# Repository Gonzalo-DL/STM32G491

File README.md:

# STM32G491
Diseño STM32G491 con USB y con header para los pines.

Además Flash de 64MB (W25Q64JWZPIM) externa con QuadSPI y dos leds en PA0 y PA1.

Conexión por USB female micro b con Buck para 3.3v.

Vin hasta 5.5v con absolute max = 6.5v.

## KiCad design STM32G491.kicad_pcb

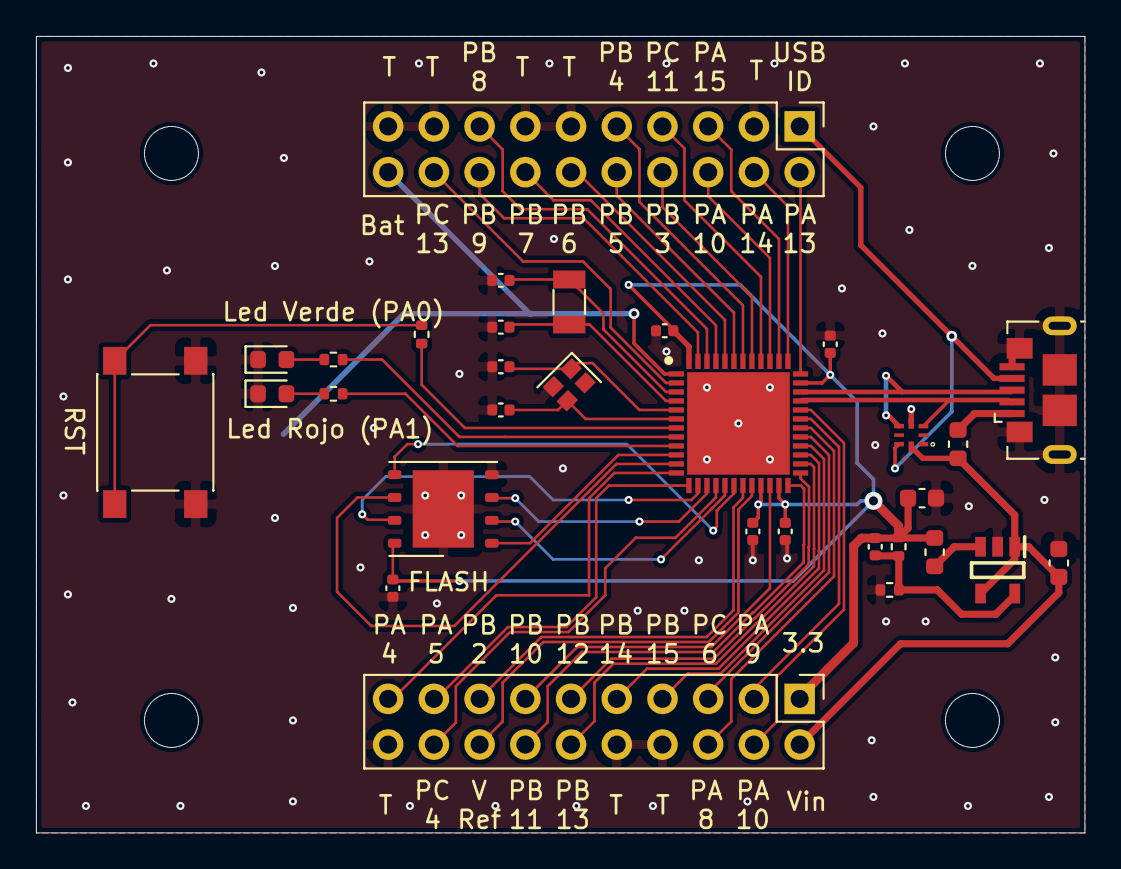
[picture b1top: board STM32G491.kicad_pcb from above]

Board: 2 copper layers, 58.2 x 44.2 mm, 32 parts (1 on the bottom side), 54 nets.

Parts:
32KHz_Crystal1: 32KHz crystal; Crystal_SMD_3215-2Pin_3.2x1.5mm
BUCK3.3: AUR9713AGH; SOT95P280X100-5N
Battery1: LIR2032; BatteryHolder_Keystone_1058_1x2032
C1(opt)1, C2(opt)1: 4p; C_0402_1005Metric
C3, C4: 12p; C_0402_1005Metric
C101, C102, C103, C104, C105: 100n; C_0402_1005Metric
C201: 4.7u; C_0603_1608Metric
C202: 10u; C_0603_1608Metric
C203: 13p; C_0402_1005Metric
Crystal_48MHz1: CX2016DB48000C0FPLC1; Crystal_SMD_2016-4Pin_2.0x1.6mm
EMI_VDDS_FILTER_USB1: BLM18HE152SN1D; L_0603_1608Metric
FLASH: W25Q64JWZPIM; WSON-8-1EP_6x5mm_P1.27mm_EP3.4x4.3mm
IC1: TPD6E004RSER; RSE0008A
J1, J2: Conn_02x10_Odd_Even; PinHeader_2x10_P2.54mm_Vertical
L101: 2.2u; L_0603_1608Metric
Led Rojo (PA1): LED; LED_0603_1608Metric
Led Verde (PA0): LED; LED_0603_1608Metric
R101: 450k; R_0402_1005Metric
R102: 100k; R_0402_1005Metric
RST: SW_DIP_x01; SW_SPST_PTS645
R_LED_ROJO1: 180; R_0402_1005Metric
R_LED_VERDE1: 220; R_0402_1005Metric
R_RST1: 100; R_0402_1005Metric
STM32: STM32G491CCU6; QFN50P700X700X60-49N-D
USB_IN1: USB_B_Micro; USB_Micro-B_GCT_USB3076-30-A

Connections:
/OSC32_IN: 32KHz_Crystal1.1, C3.1, STM32.3
/OSC32_OUT: 32KHz_Crystal1.2, C4.1, STM32.4
/OSC_IN: C1(opt)1.1, Crystal_48MHz1.1, STM32.5
/OSC_OUT: C2(opt)1.1, Crystal_48MHz1.3, STM32.6
/PA0: R_LED_VERDE1.1, STM32.8
/PA1: R_LED_ROJO1.1, STM32.9
/PA4: J2.19, STM32.12
/PA5: J2.17, STM32.13
/PA8: J2.6, STM32.30
/PA9: J2.3, STM32.31
/PA10: J2.4, STM32.32
/PA13: J1.2, STM32.36
/PA14: J1.4, STM32.37
/PA15: J1.5, STM32.38
/PB2: J2.15, STM32.19
/PB3: J1.8, STM32.41
/PB4: J1.9, STM32.42
/PB5: J1.10, STM32.43
/PB6: J1.12, STM32.44
/PB7: J1.14, STM32.45
/PB8-BOOT0: J1.15, STM32.46
/PB9: J1.16, STM32.47
/PB10: J2.13, STM32.22
/PB11: J2.14, STM32.24
/PB12: J2.11, STM32.25
/PB13: J2.12, STM32.26
/PB14: J2.9, STM32.27
/PB15: J2.7, STM32.28
/PC4: J2.18, STM32.16
/PC6: J2.5, STM32.29
/PC10: J1.6, STM32.39
/PC11: J1.7, STM32.40
/PC13: J1.18, STM32.2
/SCLK: FLASH.6, STM32.11
/SDIO0: FLASH.5, STM32.18
/SDIO1: FLASH.2, STM32.17
/SDIO2: FLASH.3, STM32.15
/SDIO3: FLASH.7, STM32.14
/USB_D+: IC1.5, STM32.34, USB_IN1.3
/USB_D-: IC1.3, STM32.33, USB_IN1.2
/USB_ID: IC1.7, J1.1, USB_IN1.4
/VBat: Battery1.1, J1.20, STM32.1
/VDD: C101.2, C102.2, C103.2, C104.2, C105.1, C202.1, C203.2, FLASH.8, J2.1, L101.2, R101.2, STM32.21, STM32.23, STM32.35, STM32.48
/VREF: J2.16, STM32.20
/Vin: BUCK3.3.1, BUCK3.3.4, C201.1, EMI_VDDS_FILTER_USB1.1, IC1.8, J2.2
/nCS: FLASH.1, STM32.10
/nRST: R_RST1.1, STM32.7
GND: BUCK3.3.2, Battery1.2, C1(opt)1.2, C2(opt)1.2, C3.2, C4.2, C101.1, C102.1, C103.1, C104.1, C105.2, C201.2, C202.2, Crystal_48MHz1.2, FLASH.4, FLASH.9, IC1.4, J1.3, J1.11, J1.13, J1.17, J1.19, J2.8, J2.10, J2.20, Led Rojo (PA1).1, Led Verde (PA0).1, R102.1, RST.1, STM32.49, USB_IN1.5, USB_IN1.6
unnamed: BUCK3.3.3, L101.1
unnamed: BUCK3.3.5, C203.1, R101.1, R102.2
unnamed: EMI_VDDS_FILTER_USB1.2, USB_IN1.1
unnamed: Led Rojo (PA1).2, R_LED_ROJO1.2
unnamed: Led Verde (PA0).2, R_LED_VERDE1.2
unnamed: RST.2, R_RST1.2

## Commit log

2021-08-31 STM32 First Commit
2021-08-31 Add gerber/drill .rar
2021-08-31 Modify PCB dimensions
2021-09-02 Agregar PNGS
